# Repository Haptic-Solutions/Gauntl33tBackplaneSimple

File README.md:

# Gauntl33tBackplaneSimple
 Simple backplane for controlling Brushless DC Gimbal motors in haptic gloves or other devices, designed at the end of 2022.  No active or passive components, just connectors.  In the future will likely make upgrades, such as taking advantage of soft I2C, but keep the board as a simple backplane.

 The Board uses SimpleFOC Mini drivers and Teensy 4.0s for controllers.

 3D Models on Printables: https://www.printables.com/model/366681-gauntl33t

 Firmware: https://github.com/Haptic-Solutions/Gauntl33tFirmware

 Demo Game: https://github.com/Haptic-Solutions/DartsGame

 Haptic Solutions Website: https://hapticsol.com

 Haptic Solutions Discord: https://discord.gg/QZYmbjJW

 Haptic Solutions Twitter: https://twitter.com/Hapticsol

 Peter Sassaman's Twitter: https://twitter.com/PeterSassaman

 Peter Sassaman's TikTok: https://www.tiktok.com/t/ZPR7QYvvF/

Link to page about SimpleFOCMini:
https://docs.simplefoc.com/simplefocmini

Link to oage about SimpleFOC:
https://simplefoc.com/

 Buy SimpleFOCMini Drivers: https://a.aliexpress.com/_mtwToBu

 Link to page about Teensy 4.0: https://www.pjrc.com/store/teensy40.html

 Buy Teensy 4.0: https://a.co/d/iZoN8jr

 Micro PSU which could be used with design to make it smaller: https://github.com/Haptic-Solutions/MicroPSU

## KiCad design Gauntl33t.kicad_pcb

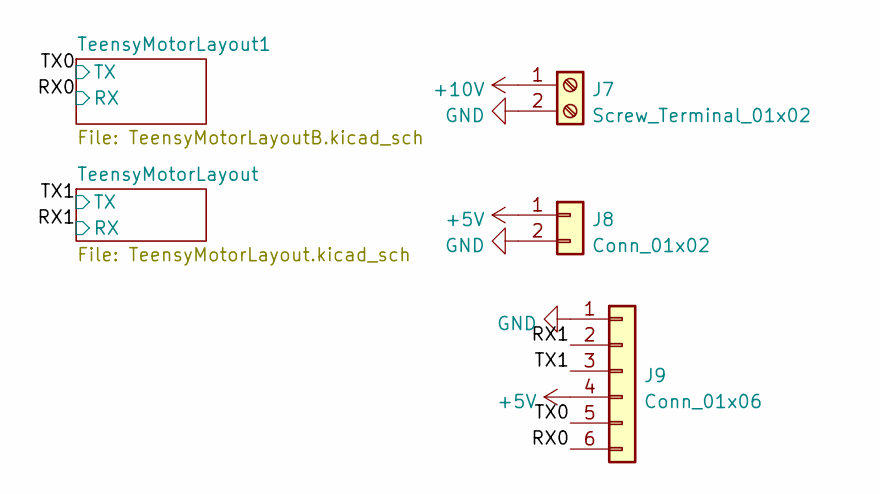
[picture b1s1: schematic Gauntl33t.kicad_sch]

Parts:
J7: Screw_Terminal_01x02; TerminalBlock_Phoenix_PT-1,5-2-3.5-H_1x02_P3.50mm_Horizontal
J8: Conn_01x02; JST_XH_B2B-XH-AM_1x02_P2.50mm_Vertical
J9: Conn_01x06; JST_XH_B6B-XH-A_1x06_P2.50mm_Vertical

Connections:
+5V: J8.1, J9.4; also elsewhere on the board
+10V: J7.1; also elsewhere on the board
/RX0: J9.6; also elsewhere on the board
/RX1: J9.2; also elsewhere on the board
/TX0: J9.5; also elsewhere on the board
/TX1: J9.3; also elsewhere on the board
GND: J7.2, J8.2, J9.1; also elsewhere on the board

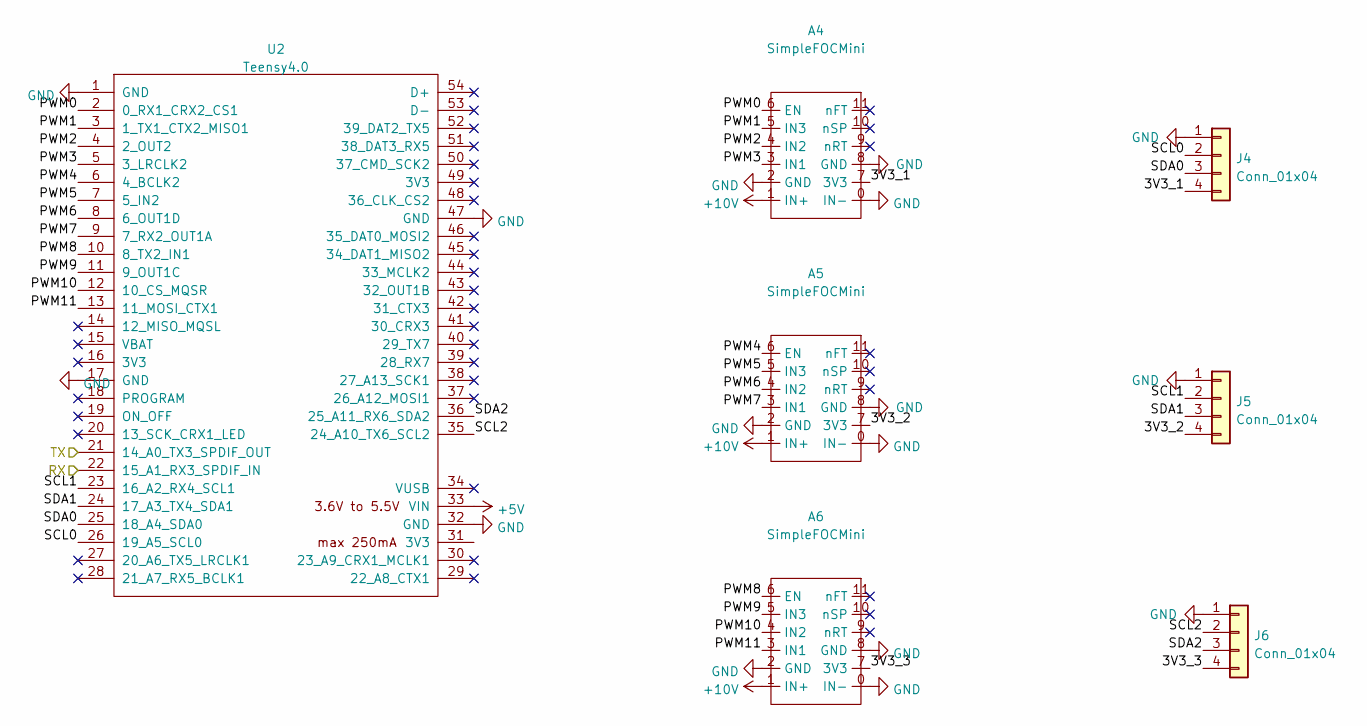
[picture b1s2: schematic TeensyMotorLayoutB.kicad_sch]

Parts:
A4, A5, A6: SimpleFOCMini
J4, J5, J6: Conn_01x04; JST_XH_S4B-XH-A-1_1x04_P2.50mm_Horizontal
U2: Teensy4.0; Teensy40

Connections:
+5V: U2.33 (VIN); also elsewhere on the board
+10V: A4.1 (IN+), A5.1 (IN+), A6.1 (IN+); also elsewhere on the board
/RX0: U2.22 (15_A1_RX3_SPDIF_IN); also elsewhere on the board
/TX0: U2.21 (14_A0_TX3_SPDIF_OUT); also elsewhere on the board
/TeensyMotorLayout1/3V3_1: A4.7 (3V3), J4.4
/TeensyMotorLayout1/3V3_2: A5.7 (3V3), J5.4
/TeensyMotorLayout1/3V3_3: A6.7 (3V3), J6.4
/TeensyMotorLayout1/PWM0: A4.6 (EN), U2.2 (0_RX1_CRX2_CS1)
/TeensyMotorLayout1/PWM1: A4.5 (IN3), U2.3 (1_TX1_CTX2_MISO1)
/TeensyMotorLayout1/PWM2: A4.4 (IN2), U2.4 (2_OUT2)
/TeensyMotorLayout1/PWM3: A4.3 (IN1), U2.5 (3_LRCLK2)
/TeensyMotorLayout1/PWM4: A5.6 (EN), U2.6 (4_BCLK2)
/TeensyMotorLayout1/PWM5: A5.5 (IN3), U2.7 (5_IN2)
/TeensyMotorLayout1/PWM6: A5.4 (IN2), U2.8 (6_OUT1D)
/TeensyMotorLayout1/PWM7: A5.3 (IN1), U2.9 (7_RX2_OUT1A)
/TeensyMotorLayout1/PWM8: A6.6 (EN), U2.10 (8_TX2_IN1)
/TeensyMotorLayout1/PWM9: A6.5 (IN3), U2.11 (9_OUT1C)
/TeensyMotorLayout1/PWM10: A6.4 (IN2), U2.12 (10_CS_MQSR)
/TeensyMotorLayout1/PWM11: A6.3 (IN1), U2.13 (11_MOSI_CTX1)
/TeensyMotorLayout1/SCL0: J4.2, U2.26 (19_A5_SCL0)
/TeensyMotorLayout1/SCL1: J5.2, U2.23 (16_A2_RX4_SCL1)
/TeensyMotorLayout1/SCL2: J6.2, U2.35 (24_A10_TX6_SCL2)
/TeensyMotorLayout1/SDA0: J4.3, U2.25 (18_A4_SDA0)
/TeensyMotorLayout1/SDA1: J5.3, U2.24 (17_A3_TX4_SDA1)
/TeensyMotorLayout1/SDA2: J6.3, U2.36 (25_A11_RX6_SDA2)
GND: A4.0 (IN-), A4.2 (GND), A4.8 (GND), A5.0 (IN-), A5.2 (GND), A5.8 (GND), A6.0 (IN-), A6.2 (GND), A6.8 (GND), J4.1, J5.1, J6.1, U2.1 (GND), U2.17 (GND), U2.32 (GND), U2.47 (GND); also elsewhere on the board

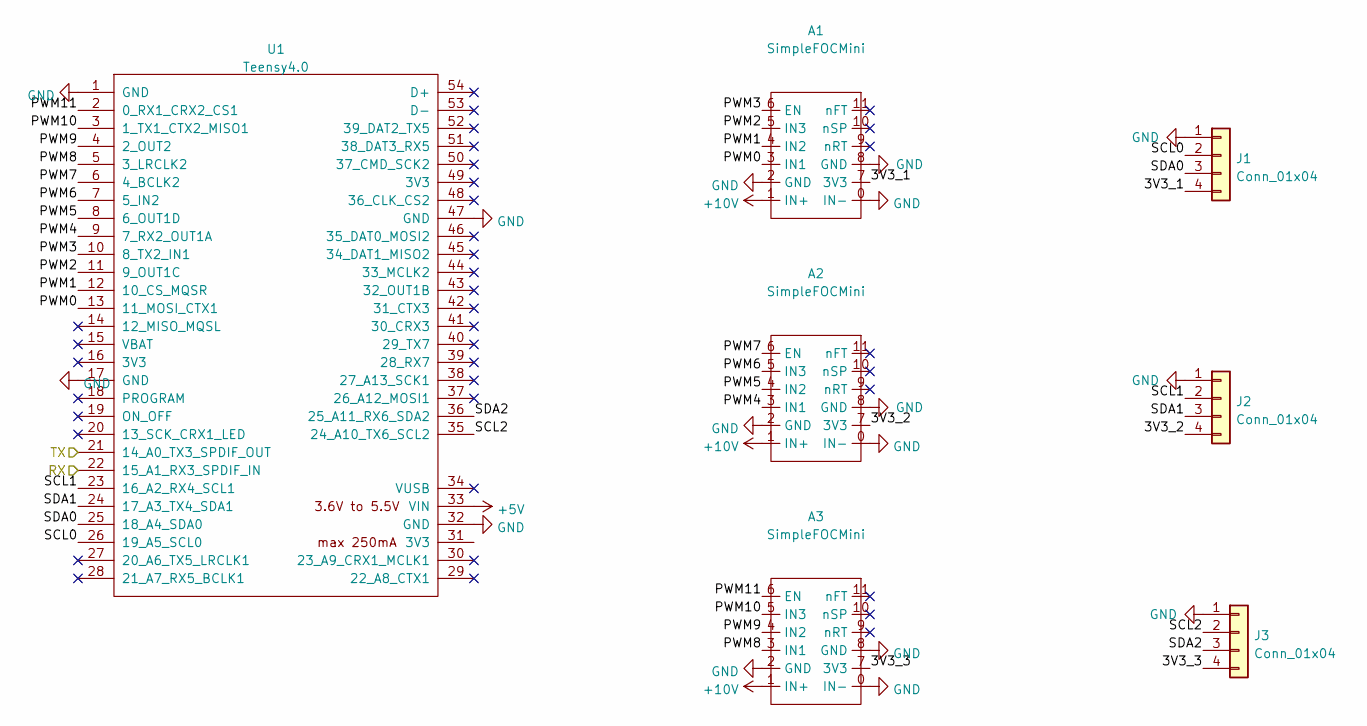
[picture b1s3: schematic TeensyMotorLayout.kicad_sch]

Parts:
A1, A2, A3: SimpleFOCMini
J1, J2, J3: Conn_01x04; JST_XH_S4B-XH-A-1_1x04_P2.50mm_Horizontal
U1: Teensy4.0; Teensy40

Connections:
+5V: U1.33 (VIN); also elsewhere on the board
+10V: A1.1 (IN+), A2.1 (IN+), A3.1 (IN+); also elsewhere on the board
/RX1: U1.22 (15_A1_RX3_SPDIF_IN); also elsewhere on the board
/TX1: U1.21 (14_A0_TX3_SPDIF_OUT); also elsewhere on the board
/TeensyMotorLayout/3V3_1: A1.7 (3V3), J1.4
/TeensyMotorLayout/3V3_2: A2.7 (3V3), J2.4
/TeensyMotorLayout/3V3_3: A3.7 (3V3), J3.4
/TeensyMotorLayout/PWM0: A1.3 (IN1), U1.13 (11_MOSI_CTX1)
/TeensyMotorLayout/PWM1: A1.4 (IN2), U1.12 (10_CS_MQSR)
/TeensyMotorLayout/PWM2: A1.5 (IN3), U1.11 (9_OUT1C)
/TeensyMotorLayout/PWM3: A1.6 (EN), U1.10 (8_TX2_IN1)
/TeensyMotorLayout/PWM4: A2.3 (IN1), U1.9 (7_RX2_OUT1A)
/TeensyMotorLayout/PWM5: A2.4 (IN2), U1.8 (6_OUT1D)
/TeensyMotorLayout/PWM6: A2.5 (IN3), U1.7 (5_IN2)
/TeensyMotorLayout/PWM7: A2.6 (EN), U1.6 (4_BCLK2)
/TeensyMotorLayout/PWM8: A3.3 (IN1), U1.5 (3_LRCLK2)
/TeensyMotorLayout/PWM9: A3.4 (IN2), U1.4 (2_OUT2)
/TeensyMotorLayout/PWM10: A3.5 (IN3), U1.3 (1_TX1_CTX2_MISO1)
/TeensyMotorLayout/PWM11: A3.6 (EN), U1.2 (0_RX1_CRX2_CS1)
/TeensyMotorLayout/SCL0: J1.2, U1.26 (19_A5_SCL0)
/TeensyMotorLayout/SCL1: J2.2, U1.23 (16_A2_RX4_SCL1)
/TeensyMotorLayout/SCL2: J3.2, U1.35 (24_A10_TX6_SCL2)
/TeensyMotorLayout/SDA0: J1.3, U1.25 (18_A4_SDA0)
/TeensyMotorLayout/SDA1: J2.3, U1.24 (17_A3_TX4_SDA1)
/TeensyMotorLayout/SDA2: J3.3, U1.36 (25_A11_RX6_SDA2)
GND: A1.0 (IN-), A1.2 (GND), A1.8 (GND), A2.0 (IN-), A2.2 (GND), A2.8 (GND), A3.0 (IN-), A3.2 (GND), A3.8 (GND), J1.1, J2.1, J3.1, U1.1 (GND), U1.17 (GND), U1.32 (GND), U1.47 (GND); also elsewhere on the board

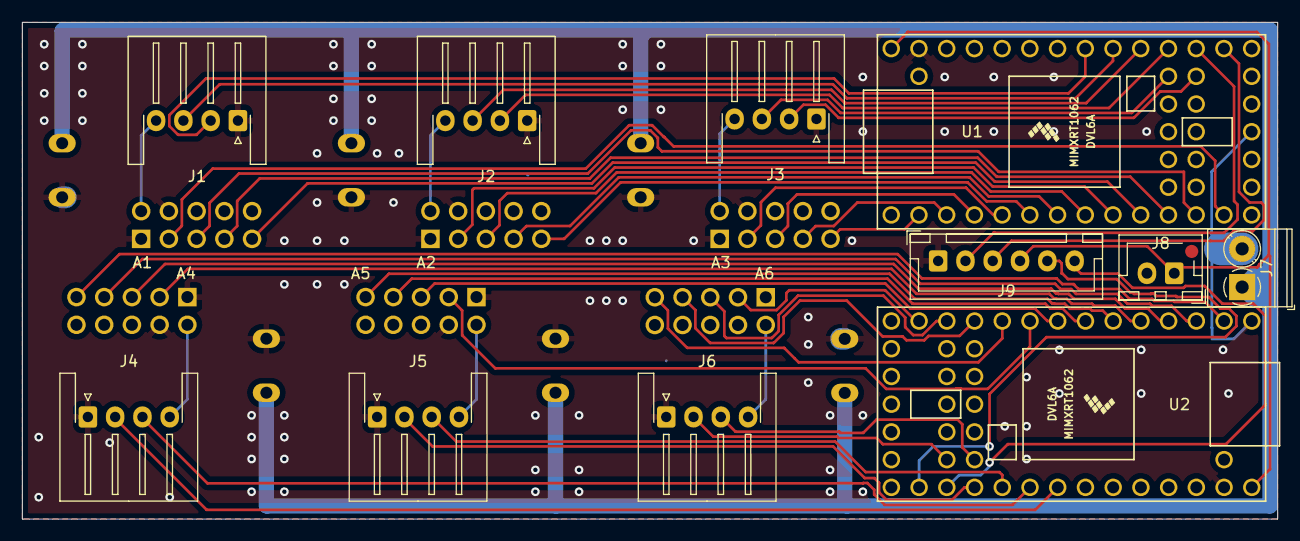
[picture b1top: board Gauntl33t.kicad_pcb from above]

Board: 2 copper layers, 115.0 x 45.5 mm, 17 parts (0 on the bottom side), 49 nets.

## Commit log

2023-10-13 Upload Initial Simple Gauntl33t Backplane from end of 2022
